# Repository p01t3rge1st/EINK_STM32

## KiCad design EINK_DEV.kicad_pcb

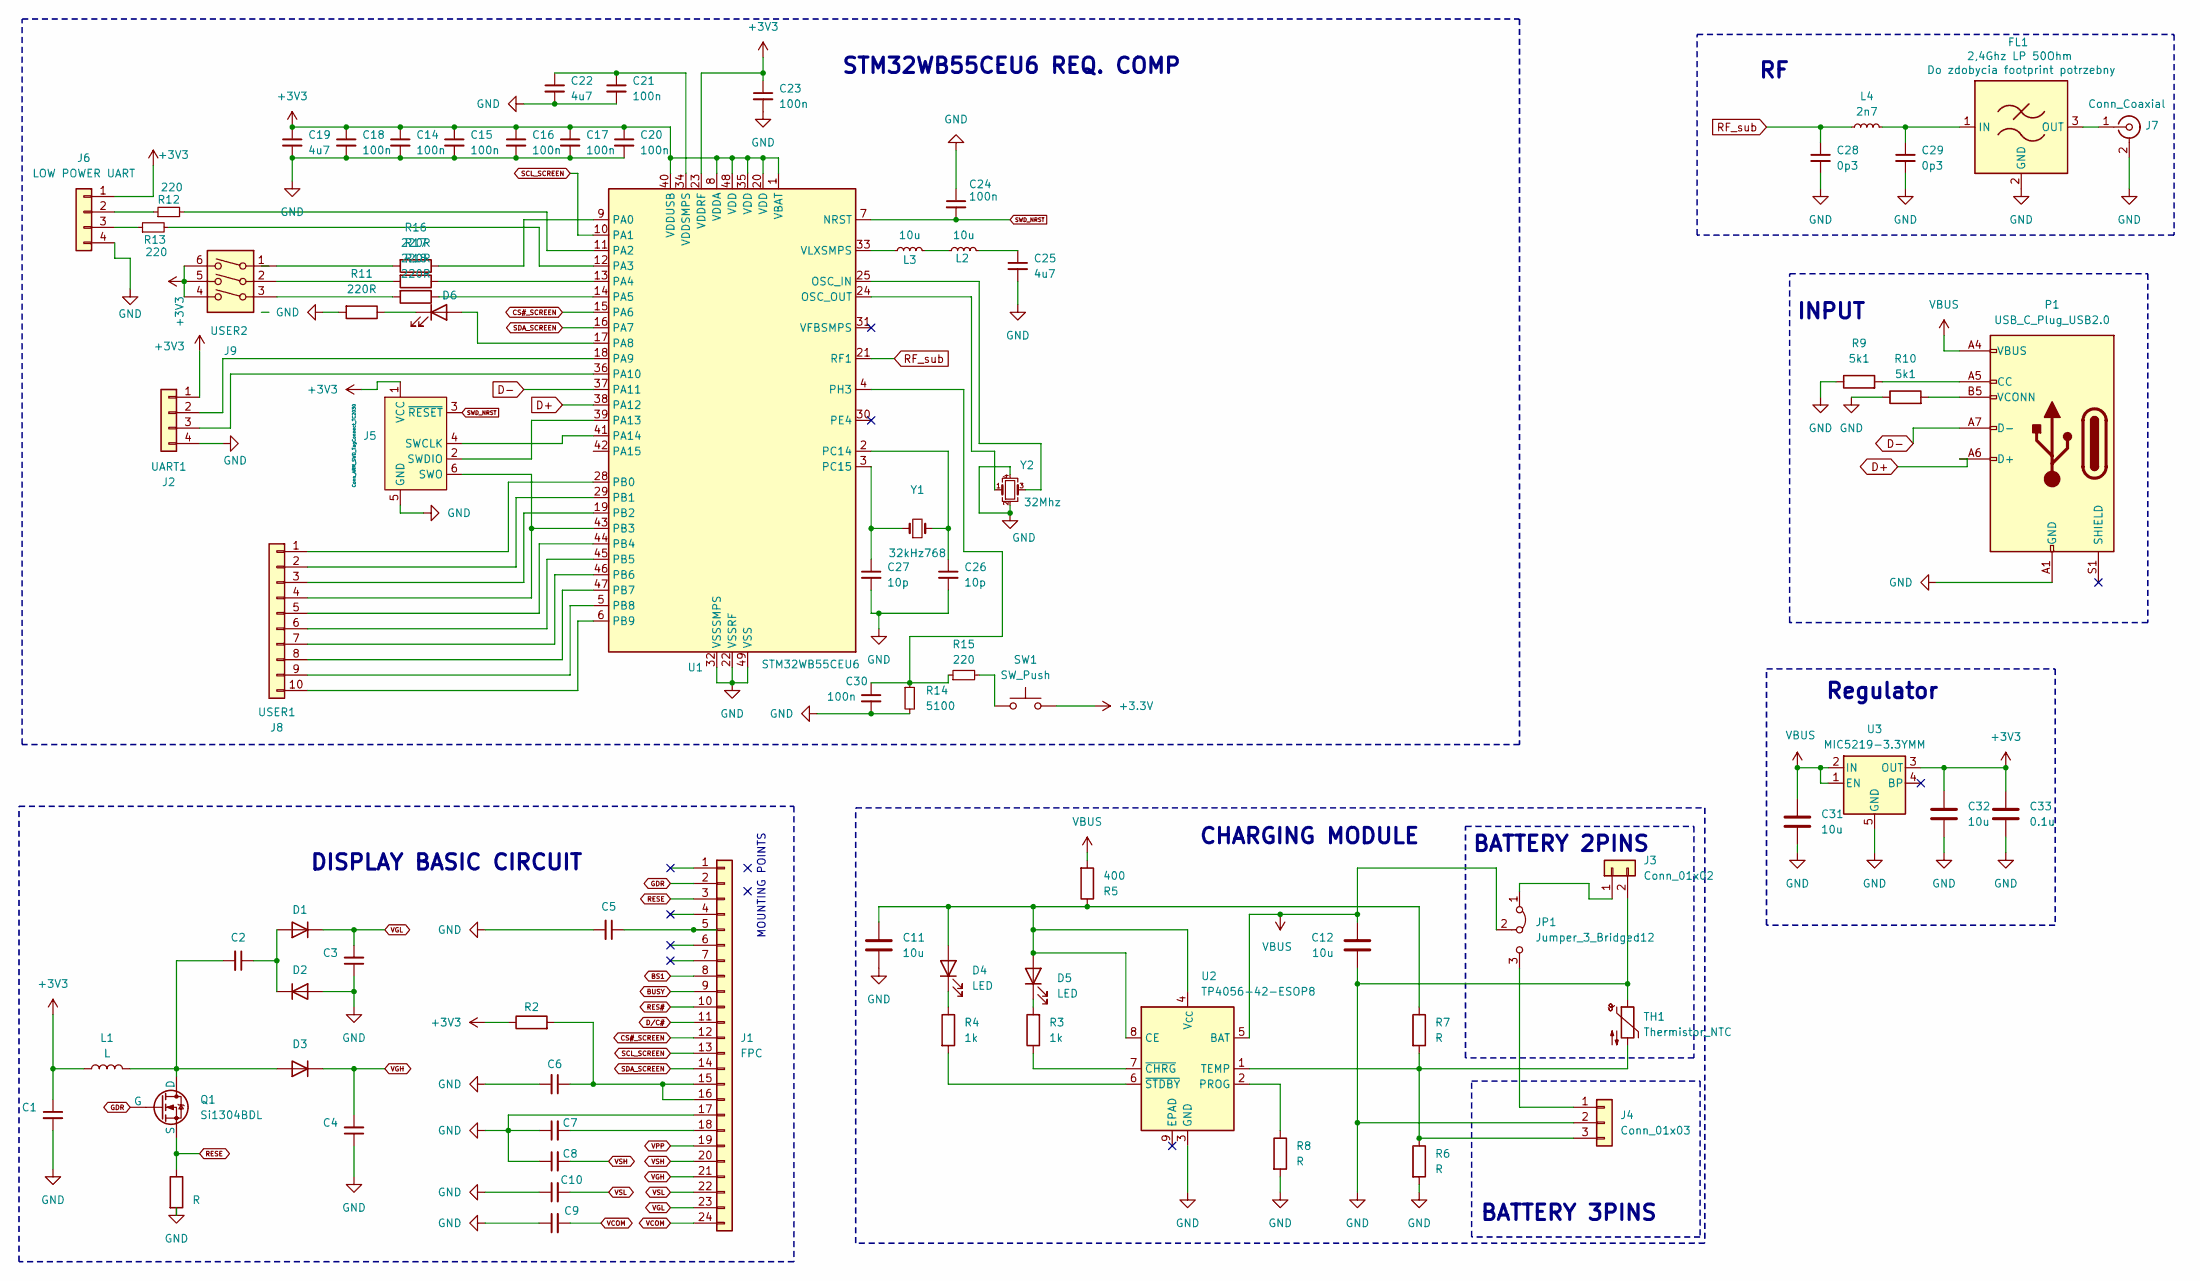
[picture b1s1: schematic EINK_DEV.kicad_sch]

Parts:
C1, C2, C5, C7, C8, C9, C10: 1u; C_0603_1608Metric
C3, C6: 1uF; C_0603_1608Metric
C4: uF; C_0603_1608Metric
C11, C12, C31, C32: 10u; C_0603_1608Metric
C14, C15, C16, C17, C18, C20, C21, C23, C24, C30: 100n; C_0603_1608Metric
C19, C22, C25: 4u7; C_0603_1608Metric
C26, C27: 10p; C_0603_1608Metric
C28, C29: 0p3; C_0603_1608Metric
C33: 0.1u; C_0603_1608Metric
D1, D2, D3: D; D_0603_1608Metric
D4, D5, D6: LED; LED_0603_1608Metric
FL1: 2,4Ghz LP 50Ohm; Filter_Mini-Circuits_FV1206
J1: FPC; TE_2-1734839-4_1x24-1MP_P0.5mm_Horizontal
J2: UART1; PinHeader_1x04_P2.54mm_Vertical
J3: Conn_01x02; Molex_KK-254_AE-6410-02A_1x02_P2.54mm_Vertical
J4: Conn_01x03; FanPinHeader_1x03_P2.54mm_Vertical
J5: Conn_ARM_SWD_TagConnect_TC2030; PinHeader_1x06_P2.54mm_Vertical
J6: LOW POWER UART; PinHeader_1x04_P2.54mm_Vertical
J7: Conn_Coaxial; U.FL_Hirose_U.FL-R-SMT-1_Vertical
J8: USER1; PinHeader_1x10_P2.54mm_Vertical
J9: USER2; SW_DIP_SPSTx03_Slide_6.7x9.18mm_W7.62mm_P2.54mm_LowProfile
JP1: Jumper_3_Bridged12; PinHeader_1x03_P2.54mm_Horizontal
L1: L; L_0603_1608Metric
L2, L3: 10u; L_0603_1608Metric
L4: 2n7; L_0603_1608Metric
P1: USB_C_Plug_USB2.0; USB_C_Receptacle_HRO_TYPE-C-31-M-12
Q1: Si1304BDL; SC-70_SI1_VIS
R1, R6, R7, R8: R; R_0603_1608Metric
R2: R2; R_0603_1608Metric
R3, R4: 1k; R_0603_1608Metric
R5: 400; R_0603_1608Metric
R9, R10: 5k1; R_0603_1608Metric
R11, R16, R17, R18: 220R; R_0603_1608Metric
R12, R13, R15: 220; R_0603_1608Metric
R14: 5100; R_0603_1608Metric
SW1: SW_Push; SW_PUSH_6mm
TH1: Thermistor_NTC; R_0603_1608Metric
U1: STM32WB55CEU6; QFN-48-1EP_7x7mm_P0.5mm_EP5.6x5.6mm
U2: TP4056-42-ESOP8; SOIC-8-1EP_3.9x4.9mm_P1.27mm_EP2.41x3.3mm_ThermalVias
U3: MIC5219-3.3YMM; MSOP-8_3x3mm_P0.65mm
Y1: 32kHz768; Crystal_SMD_2012-2Pin_2.0x1.2mm
Y2: 32Mhz; Crystal_SMD_2016-4Pin_2.0x1.6mm

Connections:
BS1: J1.8
BUSY: J1.9
CS#_SCREEN: J1.12, U1.15 (PA6)
D+: P1.A6 (D+), U1.38 (PA12)
D-: P1.A7 (D-), U1.37 (PA11)
D/C#: J1.11
GDR: J1.2, Q1.2 (G)
GND: C1.2, C3.1, C4.1, C5.2, C6.2, C7.1, C8.1, C9.1, C10.1, C11.2, C12.1, C14.2, C15.2, C16.2, C17.2, C18.2, C19.2, C20.2, C21.2, C22.2, C23.2, C24.1, C25.2, C26.2, C27.2, C28.2, C29.2, C30.2, C31.2, C32.2, C33.2, D2.2 (A), FL1.2 (GND), FL1.4 (GND), J1.17, J2.4, J3.2, J4.2, J5.5 (GND), J6.4, J7.2 (Ext), P1.A1 (GND), P1.A12 (GND), P1.B1 (GND), P1.B12 (GND), R1.2, R6.2, R8.2, R9.1, R10.1, R11.2, R14.2, TH1.1, U1.22 (VSSRF), U1.32 (VSSSMPS), U1.49 (VSS), U2.3 (GND), U3.5 (GND), U3.6 (GND), U3.7 (GND), U3.8 (GND), Y2.2, Y2.4
unnamed: C25.1, L2.2
unnamed: C2.1, D1.2 (A), D2.1 (K)
unnamed: C2.2, D3.2 (A), L1.2, Q1.1 (D)
unnamed: C11.1, D4.2 (A), D5.2 (A), R5.1, R7.1, U2.4 (V_{CC}), U2.8 (CE)
unnamed: D4.1 (K), R4.1
unnamed: D5.1 (K), R3.2
unnamed: D6.2 (A), U1.17 (PA8)
unnamed: D6.1 (K), R11.1
unnamed: C29.1, FL1.1 (IN), L4.2
unnamed: FL1.3 (OUT), J7.1 (In)
unnamed: C5.1, J1.5
unnamed: C6.1, J1.15, J1.16, R2.2
unnamed: C7.2, J1.18
unnamed: J2.2, U1.18 (PA9)
unnamed: J2.3, U1.36 (PA10)
unnamed: J3.1, JP1.1 (A)
unnamed: J4.1, JP1.3 (B)
unnamed: J4.3, R6.1, R7.2, TH1.2, U2.1 (TEMP)
unnamed: J5.4 (SWCLK), U1.41 (PA14)
unnamed: J5.2 (SWDIO), U1.39 (PA13)
unnamed: J5.6 (SWO), J8.4, U1.43 (PB3)
unnamed: J6.2, R12.1
unnamed: J6.3, R13.1
unnamed: J8.1, U1.28 (PB0)
unnamed: J8.2, U1.29 (PB1)
unnamed: J8.3, U1.19 (PB2)
unnamed: J8.5, U1.44 (PB4)
unnamed: J8.6, U1.45 (PB5)
unnamed: J8.7, U1.46 (PB6)
unnamed: J8.8, U1.47 (PB7)
unnamed: J8.9, U1.5 (PB8)
unnamed: J8.10, U1.6 (PB9)
unnamed: J9.1, R16.2
unnamed: J9.2, R17.2
unnamed: J9.3, R18.2
unnamed: L2.1, L3.2
unnamed: P1.A5 (CC), R9.2
unnamed: P1.B5 (VCONN), R10.2
unnamed: R15.2, SW1.1
unnamed: U1.25 (OSC_IN), Y2.3
unnamed: U1.24 (OSC_OUT), Y2.1
unnamed: R16.1, U1.9 (PA0)
unnamed: R12.2, U1.11 (PA2)
unnamed: R13.2, U1.12 (PA3)
unnamed: R17.1, U1.13 (PA4)
unnamed: R18.1, U1.14 (PA5)
unnamed: C26.1, U1.2 (PC14), Y1.2
unnamed: C27.1, U1.3 (PC15), Y1.1
unnamed: C30.1, R14.1, R15.1, U1.4 (PH3)
unnamed: C21.1, C22.1, U1.34 (VDDSMPS)
unnamed: L3.1, U1.33 (VLXSMPS)
unnamed: R8.1, U2.2 (PROG)
unnamed: R3.1, U2.7 (~CHRG)
unnamed: R4.2, U2.6 (~STDBY)
RES#: J1.10
RESE: J1.3, Q1.3 (S), R1.1
RF_sub: C28.1, L4.1, U1.21 (RF1)
SCL_SCREEN: J1.13, U1.10 (PA1)
SDA_SCREEN: J1.14, U1.16 (PA7)
SWD_NRST: C24.2, J5.3 (~RESET), U1.7 (NRST)
VBUS: C12.2, C31.1, JP1.2 (C), P1.A4 (VBUS), P1.A9 (VBUS), P1.B4 (VBUS), P1.B9 (VBUS), R5.2, U2.5 (BAT), U3.1 (EN), U3.2 (IN)
VCOM: C9.2, J1.24
VGH: C4.2, D3.1 (K), J1.21
VGL: C3.2, D1.1 (K), J1.23
VPP: J1.19
VSH: C8.2, J1.20
VSL: C10.2, J1.22

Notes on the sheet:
Regulator
MOUNTING POINTS
BATTERY 2PINS
STM32WB55CEU6 REQ. COMP
BATTERY 3PINS
INPUT
CHARGING MODULE
DISPLAY BASIC CIRCUIT

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
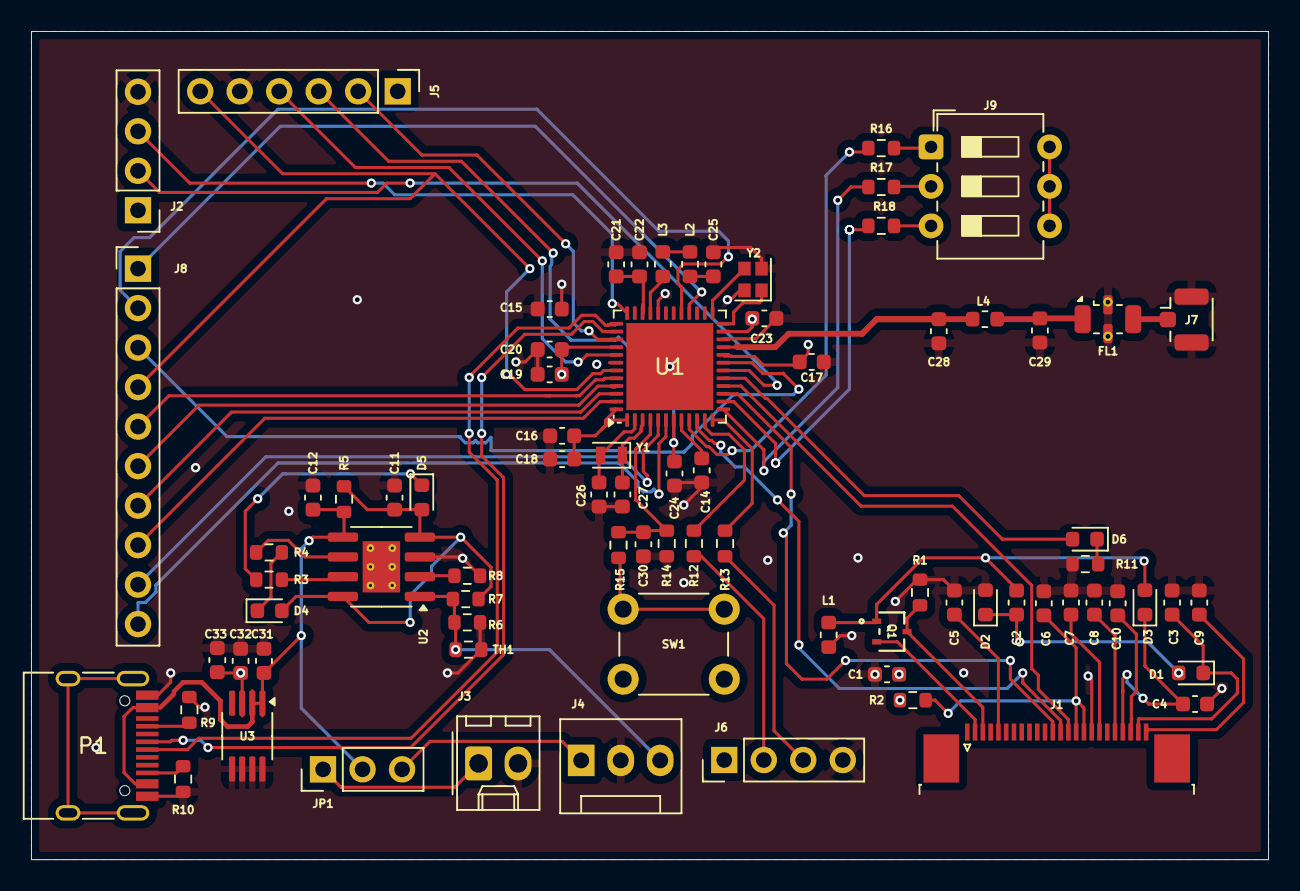
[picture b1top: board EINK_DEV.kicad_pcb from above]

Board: 4 copper layers, 79.5 x 53.3 mm, 80 parts (0 on the bottom side), 71 nets.

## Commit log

2025-03-20 Init
    Schematy podstawowego połączenia do wyświetlacza dodane
2025-04-04 Add micro-USB input
2025-04-04 Add D+ and D- flag
2025-04-04 Add TP4056 module
2025-04-04 Add charging module
2025-04-04 Add connector instead of battery
2025-04-04 Add options for baterry connector
    2Pin and 3Pin Connector are available. Depends on a jumper placing.
2025-04-07 Add onnections from battery to BAT pin
    Add connections from 2 and 3Pin connectors to BAT pin.
2025-04-08 Added BATT protection
2025-04-08 Wymagane podzespoły do funkcjonowania płytki
    - dodano RF dla ble
    - dodano kryształy
    - dodano headaery do programatora
    problemy:
    - nieciągłość w liniach napięcia (vbus,3.3 itd): trzeba zuinifikować
    - miejsce na pin headery dla programisty/elektronika
2025-04-15 Add a linear regulator from USB
2025-04-15 Add GND Pins in RF section
2025-04-15 Add NC flag to EPAD Pin on Charging Module
2025-04-15 Assign value to capacitor C32
2025-04-15 Poprawka Zasilania
2025-04-24 Remove charging battery module protection
2025-04-24 Add USB C
2025-04-24 Add LDO
2025-04-24 LDO v2
2025-04-24 Edit connection
2025-04-24 SPI connection to MCU, module replacemnt (w ant.)
2025-04-24 Revert "SPI connection to MCU, module replacemnt (w ant.)"
    This reverts commit eeb590f0e93481794f65d485278f1cb99dabf3cf.
2025-04-24 SPI conn, bigger sheet, rf mod replace
2025-05-05 Dużo zmian ale to jeszcze nie koniec
2025-05-06 PCB gotowa
2025-05-26 Uporzadkowanie komponentów HF
2025-05-29 Płytka prawie końcowa
    - prawidłowa impredancja
    - prawidłowe warstwy GND i 3v3
    - rozłożenie prawidłowe C
    - do poprawienia napisy
2025-05-30 Edit labels on PCB
2025-06-04 Final changes
    Fixed RF shape
    Fixed USB C conn
    Fixed a lot of DRCs
    Fixed broken Footprints
2025-06-23 Ostateczny commit chyba
2025-06-23 To juz ostatni obiecuje
